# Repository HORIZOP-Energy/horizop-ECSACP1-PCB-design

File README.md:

# HORIZOP Energy's EV Charging Station Prototype 1 PCB Design in KiCad and Solidworks

KiCad design files of a controller board for Type-2 charging (IEC 61851) of EVs.

See [Schematic](Media/HE_ECSACP1_PCB_Schematic.png) and [3d-view](Renders/Assembly_HE_ECSACP1_PCB_V9_With_ESP_WROVER_KIT_V4.1_Final_Render.png).

See [horizop-ECSACP1-firmware](https://github.com/HORIZOP-Energy/horizop-ECSACP1-firmware) for more 
information on the entire prototype.

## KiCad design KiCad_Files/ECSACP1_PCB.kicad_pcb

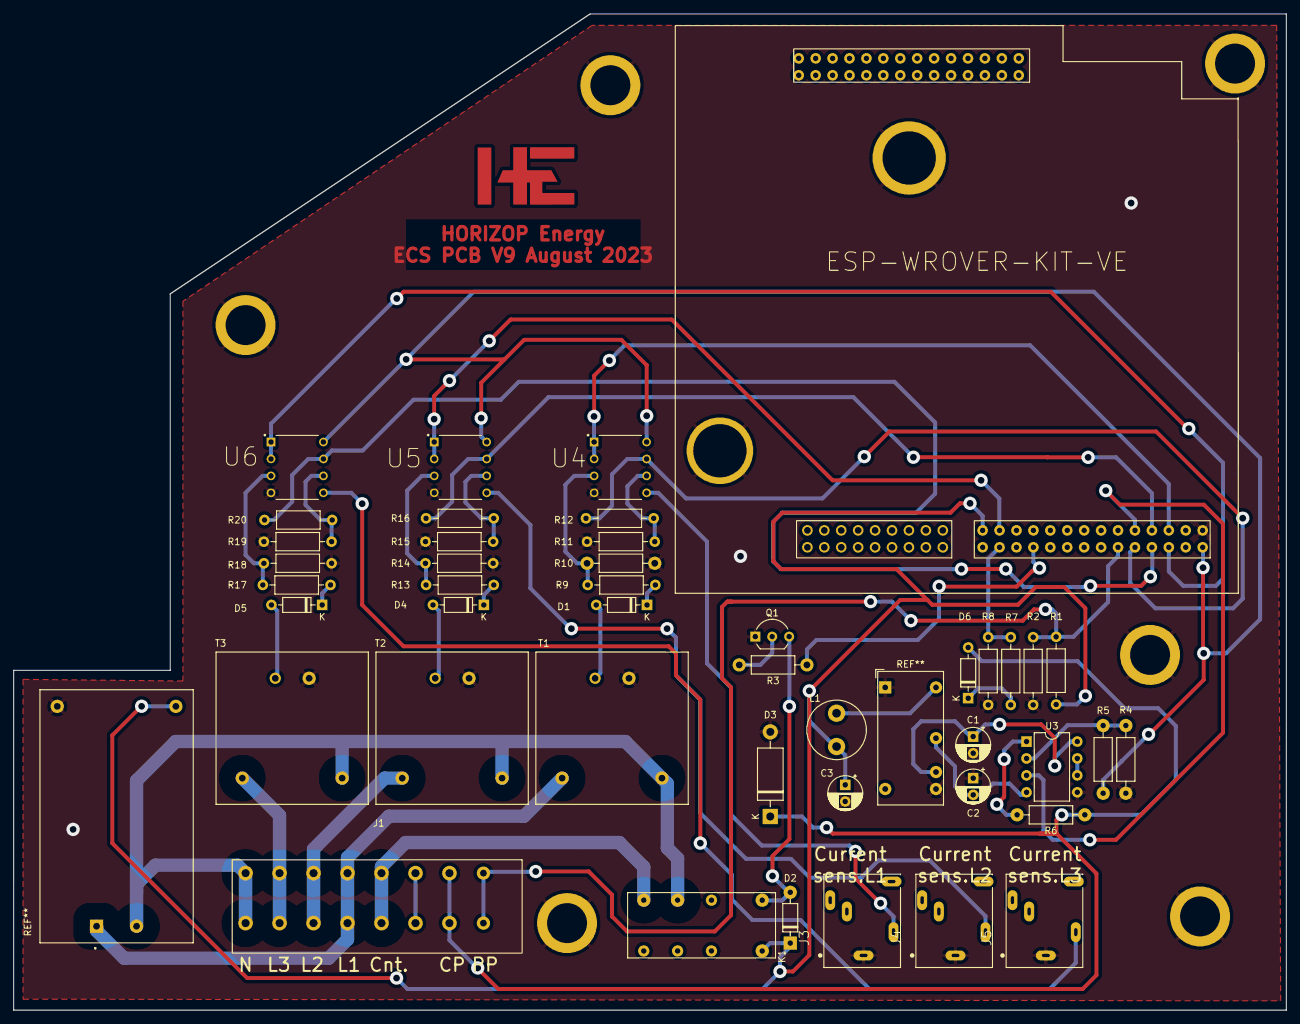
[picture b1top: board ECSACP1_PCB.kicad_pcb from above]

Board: 2 copper layers, 191.0 x 149.5 mm, 43 parts (1 on the bottom side), 41 nets.

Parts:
C1, C2: 1uf; CP_Radial_D5.0mm_P2.50mm
C3: 2.2uf/50V; CP_Radial_D5.0mm_P2.50mm
D1, D2, D4, D5, D6: 1N4148; D_DO-35_SOD27_P7.62mm_Horizontal
D3: TVS-P6KE16CA; D_DO-15_P12.70mm_Horizontal
J1: Connector1; Bornier la5dher
J3, J4, J5: SJ1-3515N; CUI_SJ1-3515N
L1: 18uH; L_Radial_D8.7mm_P5.00mm_Fastron_07HCP
Q1: PN2222A; TO-92_Inline_Wide
R1, R2, R6: 1k; R_Axial_DIN0207_L6.3mm_D2.5mm_P10.16mm_Horizontal
R3: 330; R_Axial_DIN0207_L6.3mm_D2.5mm_P10.16mm_Horizontal
R4, R5: 120k; R_Axial_DIN0207_L6.3mm_D2.5mm_P10.16mm_Horizontal
R7: 180k; R_Axial_DIN0207_L6.3mm_D2.5mm_P10.16mm_Horizontal
R8: 47k; R_Axial_DIN0207_L6.3mm_D2.5mm_P10.16mm_Horizontal
R9, R13, R17: 100k; R_Axial_DIN0207_L6.3mm_D2.5mm_P10.16mm_Horizontal
R10, R11, R12, R14, R15, R16, R18, R19, R20: 10k; R_Axial_DIN0207_L6.3mm_D2.5mm_P10.16mm_Horizontal
Ref**: ESP-WROVER-KIT-VE
T1, T2, T3: VB_05-1-12
U3: LT1498IN8; DIP-8_W7.62mm
U4, U5, U6: MCP602T; DIP787W46P254L927H533Q8

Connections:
+3V3: R5.2, Ref**.1, U4.8, U5.8, U6.8
+5V: C3.1, D2.1, L1.2, R1.2, Ref**.28
+12VDC: C1.1, U3.8
-12VDC: C2.2, U3.4
/PP: J1.13, R1.1, R2.2, Ref**.6
CP: D3.1, D6.2, J1.14, R6.1
CP_READ: R7.1, R8.2, Ref**.13
CURRENT_SENS_L1_READ: R12.2, Ref**.5, U4.7
CURRENT_SENS_L2_READ: R16.2, Ref**.18, U5.7
CURRENT_SENS_L3_READ: R20.2, Ref**.4, U6.7
CUR_SENS_L1: J3.2, U4.5
CUR_SENS_L2: J4.2, U5.5
CUR_SENS_L3: J5.2, U6.5
DC_RELAY: R3.1, Ref**.11
GND: C1.2, C2.1, C3.2, D3.2, J3.1, J4.1, J5.1, Q1.1, R2.1, R4.1, R8.1, R10.2, R11.1, R14.2, R15.1, R18.2, R19.1, Ref**.15, T1.4, T2.4, T3.2, U3.5, U4.4, U5.4, U6.4
MAINS_L1: J1.17, T1.1
MAINS_L2: J1.18, T2.1
MAINS_L3: J1.19, T3.1
MAINS_N: J1.20, T1.2, T2.2, T3.2
unnamed: D1.1, R9.1
unnamed: D1.2, T1.3
unnamed: D2.2, Q1.3
unnamed: D4.1, R13.1
unnamed: D4.2, T2.3
unnamed: D5.1, R17.1
unnamed: D5.2, T3.3
unnamed: D6.1, R7.2
unnamed: Q1.2, R3.2
unnamed: R4.2, R5.1, U3.2
unnamed: R6.2, U3.1
unnamed: R9.2, R10.1, U4.3
unnamed: R11.2, R12.1, U4.6
unnamed: R13.2, R14.1, U5.3
unnamed: R15.2, R16.1, U5.6
unnamed: R17.2, R18.1, U6.3
unnamed: R19.2, R20.1, U6.6
unnamed: U3.6, U3.7
PWM: Ref**.19, U3.3
VOLTAGE_SENS_L1_READ: Ref**.17, U4.1, U4.2
VOLTAGE_SENS_L2_READ: Ref**.27, U5.1, U5.2
VOLTAGE_SENS_L3_READ: Ref**.3, U6.1, U6.2

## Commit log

2023-11-17 Initial commit PCB version 1
2023-11-17 first modifications for pcb design v2 1mm
2023-11-17 modifications for pcb design: version 2.2 1mm
2023-11-17 modifications for pcb design: version 3
2023-11-17 modifications for pcb design version 4: like v3 but with both faces soldering
2023-11-17 modifications for pcb design v6: like v4 but with modified jack and 0.8 vias
2023-11-17 modifications for pcb design v7: like v5 but with modified jack and 0.8mm vias
2023-11-17 final printed version: v9: like v7 but with 0.6mm vias
2023-11-17 added 3d renderings and media
2023-11-17 rename render
2023-11-17 renaming
2023-11-17 added solidworks files and renders
2023-11-17 deleted readme
2023-11-17 deleted license and modified readme
2023-11-17 renamed prints
